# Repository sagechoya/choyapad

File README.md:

# choyapad

A 3x3 + 1 macropad with a 128x32 OLED, built around an RP2040 Pro Micro. Through-hole parts only, so it's easy to hand-solder.

## What's here

| Folder | Contents |
|---|---|
| `pcb/` | KiCad 10 project (schematic + PCB) |
| `gerbers/`, `gerbers.zip` | Fabrication files, ready to upload to JLCPCB or similar (2-layer) |
| `case/` | 3D-printable case: cover plate + tray (STL / 3MF) and the Python scripts that generate them |
| `firmware/choyapad/` | QMK keyboard definition and default keymap |

## Bill of materials

| Qty | Ref | Part | Notes |
|---|---|---|---|
| 10 | S1-S10 | MX-style switches | Soldered (no hot-swap sockets) |
| 10 | D1-D9, D11 | 1N4148 diode, DO-35 through-hole | On the back of the board (there is no D10) |
| 1 | U1 | RP2040 Pro Micro | On the back, USB-C out of the right edge; plus pin headers |
| 1 | J1 | 0.91" 128x32 I2C OLED (SSD1306) | 4-pin GND / VCC / SCL / SDA; plus a 4-pin header |
| 10 | - | 1U MX keycaps | |
| 4 | - | M2 screws | For the 4 mounting holes |

## Firmware

Copy `firmware/choyapad` into `qmk_firmware/keyboards/`, then:

    qmk compile -kb choyapad -km default

Pins: columns GP2, GP4, GP3; rows GP5-GP8 (COL2ROW); OLED on I2C0 (SDA GP12, SCL GP13).

The default keymap includes some Guild Wars 2 chat macros and a Windows launcher macro
(`C:\path\to\launch_games.bat`). Edit `keymaps/default/keymap.c` to suit yourself.

To flash: hold BOOT on the Pro Micro while plugging it in (or double-tap RST, or hold the top-left key),
then copy the `.uf2` onto the drive that appears.

## Case

- `3x3_+1_OLED_2026.9.26c_cover-plate_no-pin-hole.stl` / `.3mf`: top plate with the OLED window. The OLED header pins
  must be trimmed to sit no more than 6.2 mm above the bottom of the main PCB.
- `choyapad-tray-TILT10-2color.3mf`: tray tilted 10 degrees, with "choyapad" text on the bottom as a second colour
  (Bambu Studio project for an A1, two manual filament swaps).
- `3x3_+1_OLED_2026.9.26c_tray-choya.stl`: the same tilted tray as a single-colour STL.

The `build_*.py` scripts regenerate the models (`pip install manifold3d shapely numpy pillow`).
Set the font path in `choya_art.py` (`/path/to/DejaVuSans-Bold.ttf`) to a DejaVu Sans Bold on your system first.

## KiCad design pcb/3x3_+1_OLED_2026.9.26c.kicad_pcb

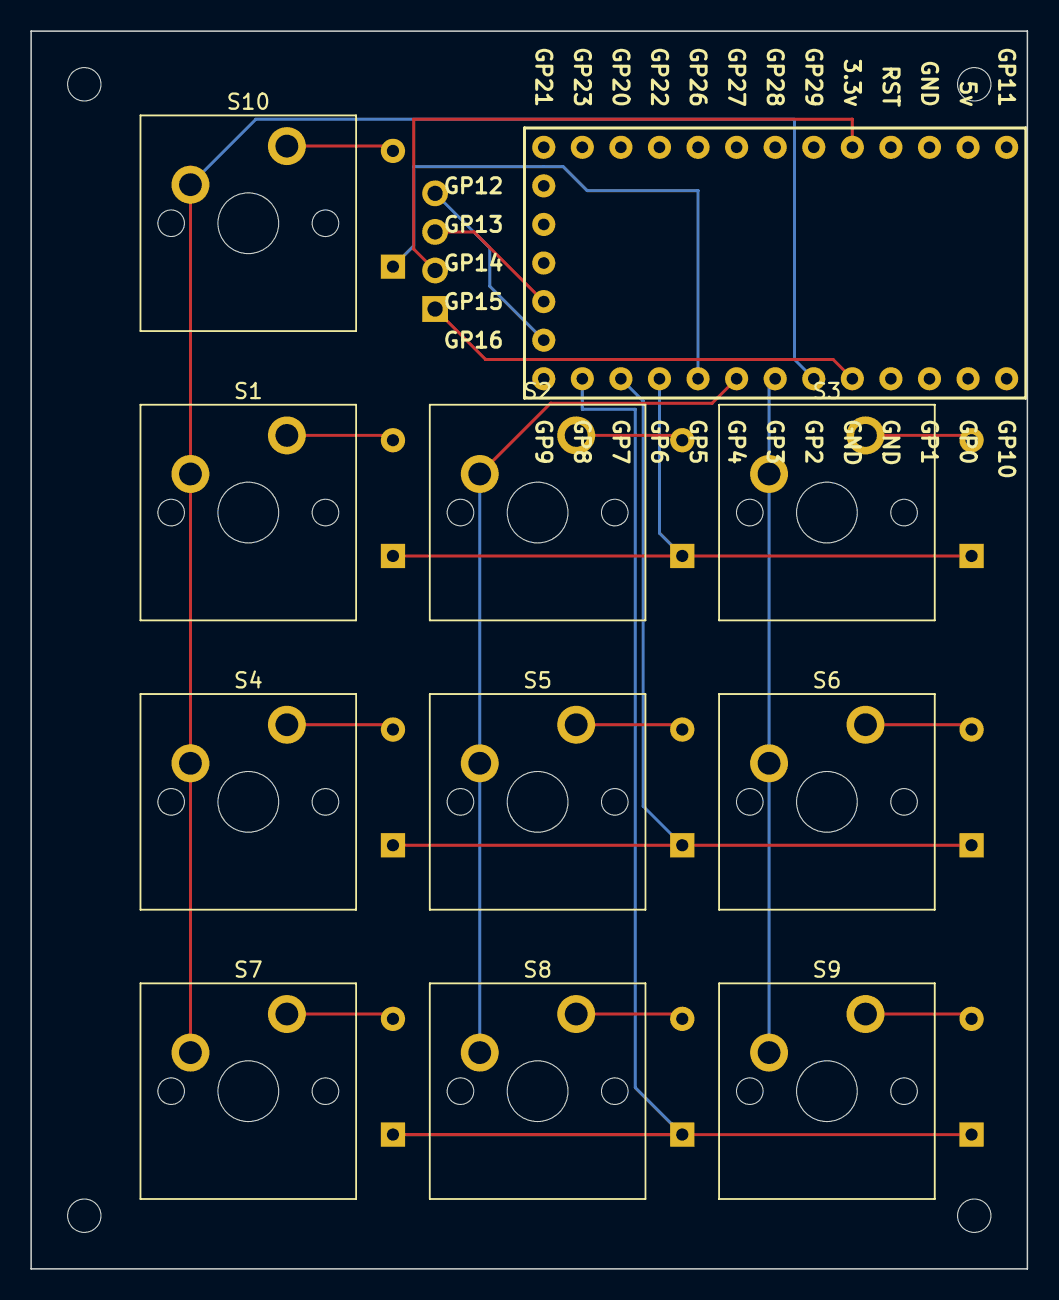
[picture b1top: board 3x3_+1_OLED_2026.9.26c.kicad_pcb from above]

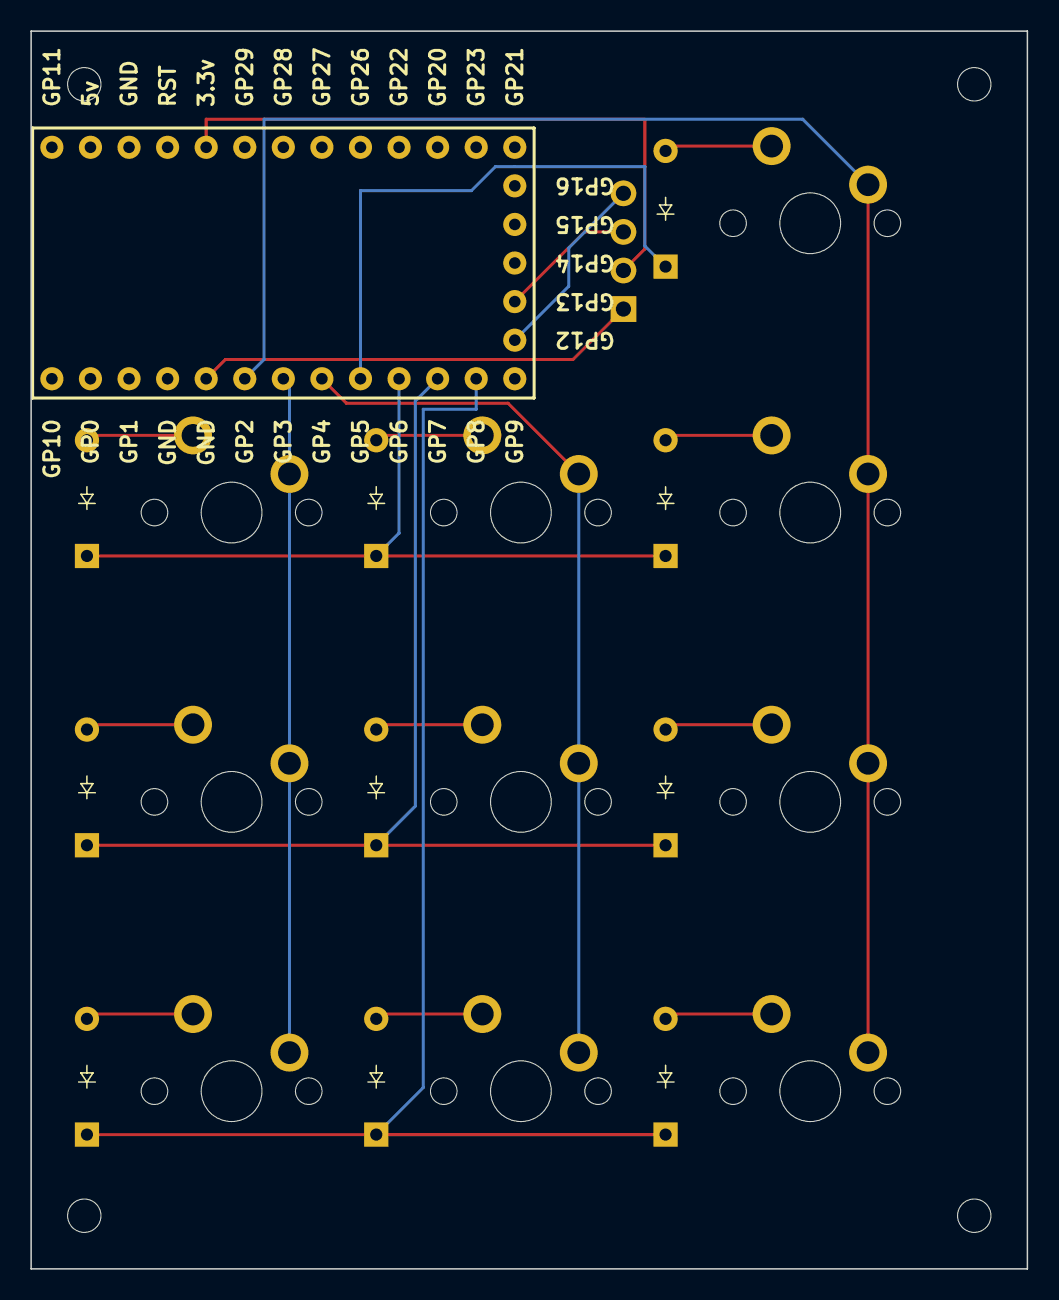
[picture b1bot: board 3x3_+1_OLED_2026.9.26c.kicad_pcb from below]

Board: 2 copper layers, 65.6 x 81.5 mm, 26 parts (11 on the bottom side), 21 nets.

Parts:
D1, D2, D3, D4, D5, D6, D7, D8, D9, D11: Diode_DO-35
H1, H2, H3, H4: MountingHole_M2; MountingHole_2.2mm_M2
J1: OLED_128x32
S1, S2, S3, S4, S5, S6, S7, S8, S9, S10: MX_PCB_1.00u
U1: RP2040_Pro_Micro

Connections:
Column 0: S1.1, S4.1, S7.1, S10.1, U1.6 (GP2)
Column 1: S2.1, S5.1, S8.1, U1.8 (GP4)
Column 2: S3.1, S6.1, S9.1, U1.7 (GP3)
unnamed: D1.2 (A), S1.2
unnamed: D2.2 (A), S2.2
unnamed: D3.2 (A), S3.2
unnamed: D4.2 (A), S4.2
unnamed: D5.2 (A), S5.2
unnamed: D6.2 (A), S6.2
unnamed: D7.2 (A), S7.2
unnamed: D8.2 (A), S8.2
unnamed: D9.2 (A), S9.2
unnamed: D11.2 (A), S10.2
OLED_3.3V: J1.2 (VCC), U1.27 (3.3v)
OLED_GND: J1.1 (GND), U1.5 (GND)
OLED_SCL: J1.3 (SCL), U1.15 (GP13)
OLED_SDA: J1.4 (SDA), U1.14 (GP12)
Row 0: D11.1 (K), U1.9 (GP5)
Row 1: D1.1 (K), D2.1 (K), D3.1 (K), U1.10 (GP6)
Row 2: D4.1 (K), D5.1 (K), D6.1 (K), U1.11 (GP7)
Row 3: D7.1 (K), D8.1 (K), D9.1 (K), U1.12 (GP8)
